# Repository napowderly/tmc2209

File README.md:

# tmc2209

Wooohooo a new package!

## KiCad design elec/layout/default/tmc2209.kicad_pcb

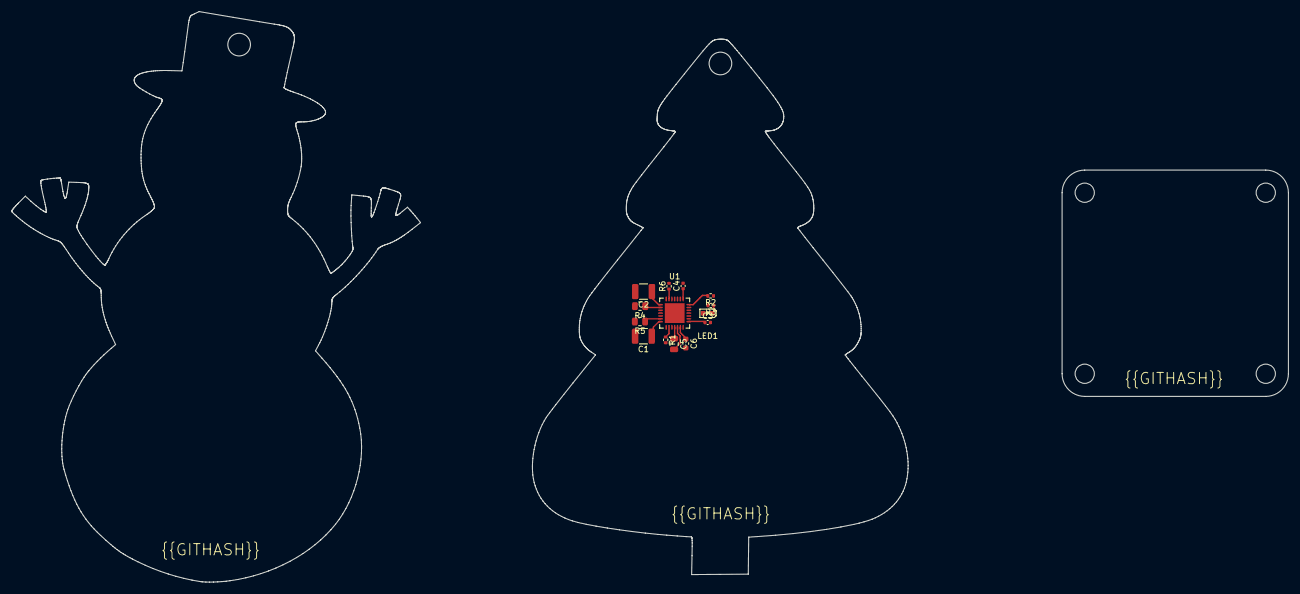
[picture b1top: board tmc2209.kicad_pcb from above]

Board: 2 copper layers, 66.4 x 94.6 mm, 14 parts (0 on the bottom side), 14 nets.

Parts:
C1, C2: Multilayer Ceramic Capacitors MLCC - SMD/SMT 2.2u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; C1210
C3: Multilayer Ceramic Capacitors MLCC - SMD/SMT 2.2u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; C0402
C4: Multilayer Ceramic Capacitors MLCC - SMD/SMT 100n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; C0402
C5: Multilayer Ceramic Capacitors MLCC - SMD/SMT 22nF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; C0805
C6: Multilayer Ceramic Capacitors MLCC - SMD/SMT 100n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; C0603
LED1: LED0603-RD
R1, R6: Chip Resistor - Surface Mount 110KOhms ±5% 1/16W 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; R0402
R2: Chip Resistor - Surface Mount 1.1KOhms ±5% 1/16W 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; R0402
R3: Chip Resistor - Surface Mount 120Ohms ±5% 1/16W 0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; R0402
R4, R5: Chip Resistor - Surface Mount 0.12Ohms ±5% 1/8W 0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; R0805
U1: QFN-28_L5.0-W5.0-P0.50-BL-EP

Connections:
_5vout: C3.1, U1.8
bra: R4.1, U1.23
brb: R5.1, U1.27
cathode: LED1.1, R3.1
cpi: C5.2, U1.5
cpo: C5.1, U1.4
diag: LED1.2, U1.11
enn: R1.1, U1.2
gnd: C1.2, C2.2, C3.2, C4.2, R1.2, R3.2, R4.2, R5.2, R6.2, U1.3, U1.7, U1.18, U1.29
pdn_uart: R2.2, U1.14
stdby: R6.1, U1.20
vcc: C1.1, C2.1, C6.2, U1.22, U1.28
vcc_io: C4.1, U1.15
vcp: C6.1, U1.6

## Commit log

2024-02-12 Configure project
2024-02-13 intial commit
2024-02-13 added layout
2024-02-15 added enable button
